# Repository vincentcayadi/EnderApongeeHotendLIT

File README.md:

# Ender Apongee Hotend Lit

This is a remix from [ORBITER PROJECTs's Apogee Toolhead Hotend Lit White LED PCB](https://www.orbiterprojects.com/apogee-ender-3-v2/). I just changed the overall asthetic of the board. E.g the silkscreen and the placement of the components.

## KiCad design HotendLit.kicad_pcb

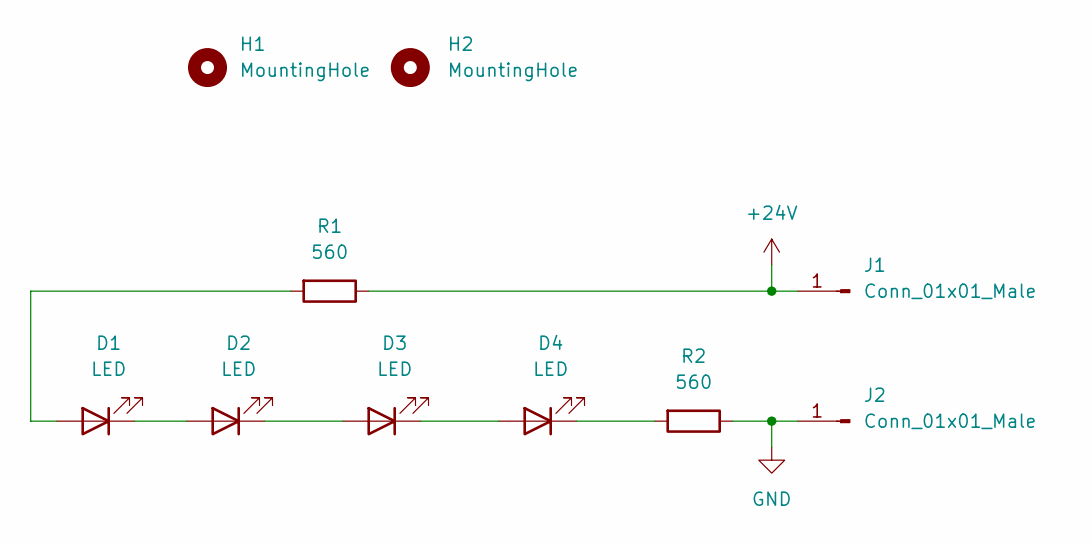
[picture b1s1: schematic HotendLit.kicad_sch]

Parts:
D1, D2, D3, D4: LED; led2835
H1, H2: MountingHole; MountingHole_2.5mm_Pad_Via
J1, J2: Conn_01x01_Male; SolderPad
R1, R2: 560; res0603

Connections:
+24V: J1.1, R1.1
GND: J2.1, R2.1
unnamed: D1.2 (A), R1.2
unnamed: D1.1 (K), D2.2 (A)
unnamed: D2.1 (K), D3.2 (A)
unnamed: D3.1 (K), D4.2 (A)
unnamed: D4.1 (K), R2.2

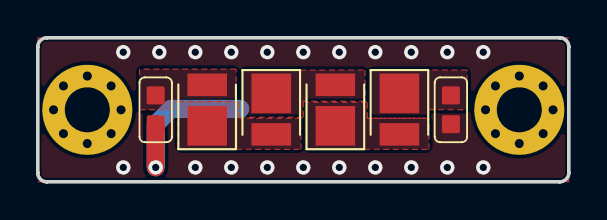
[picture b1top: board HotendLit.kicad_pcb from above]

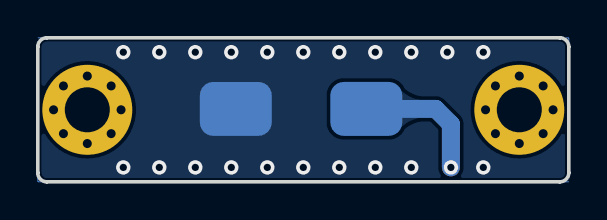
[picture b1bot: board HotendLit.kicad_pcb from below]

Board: 2 copper layers, 29.5 x 8.0 mm, 10 parts (2 on the bottom side), 7 nets.

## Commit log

2024-02-08 Init Commit
2024-02-08 README
2024-02-08 DS Store
